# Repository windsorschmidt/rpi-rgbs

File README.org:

#+OPTIONS: toc:nil

* About

TV-compatible RGBS video output board for Raspberry Pi.

[[rpi-rgbs.png?raw=true]]

* Features

- 6-bit R-2R video DAC with buffered 75Ω output on VGA (DE-15) connector
- Composite video sync generator using XNOR logic gates
- Low-pass reconstruction filter audio DAC output on 3.5" phono jack

* Status

Revision 3 tested working with a Raspberry Pi 4.

* License

Circuit schematic and PCB layout are licensed under CERN-OHL-S v2.

See [[LICENSE.txt]].

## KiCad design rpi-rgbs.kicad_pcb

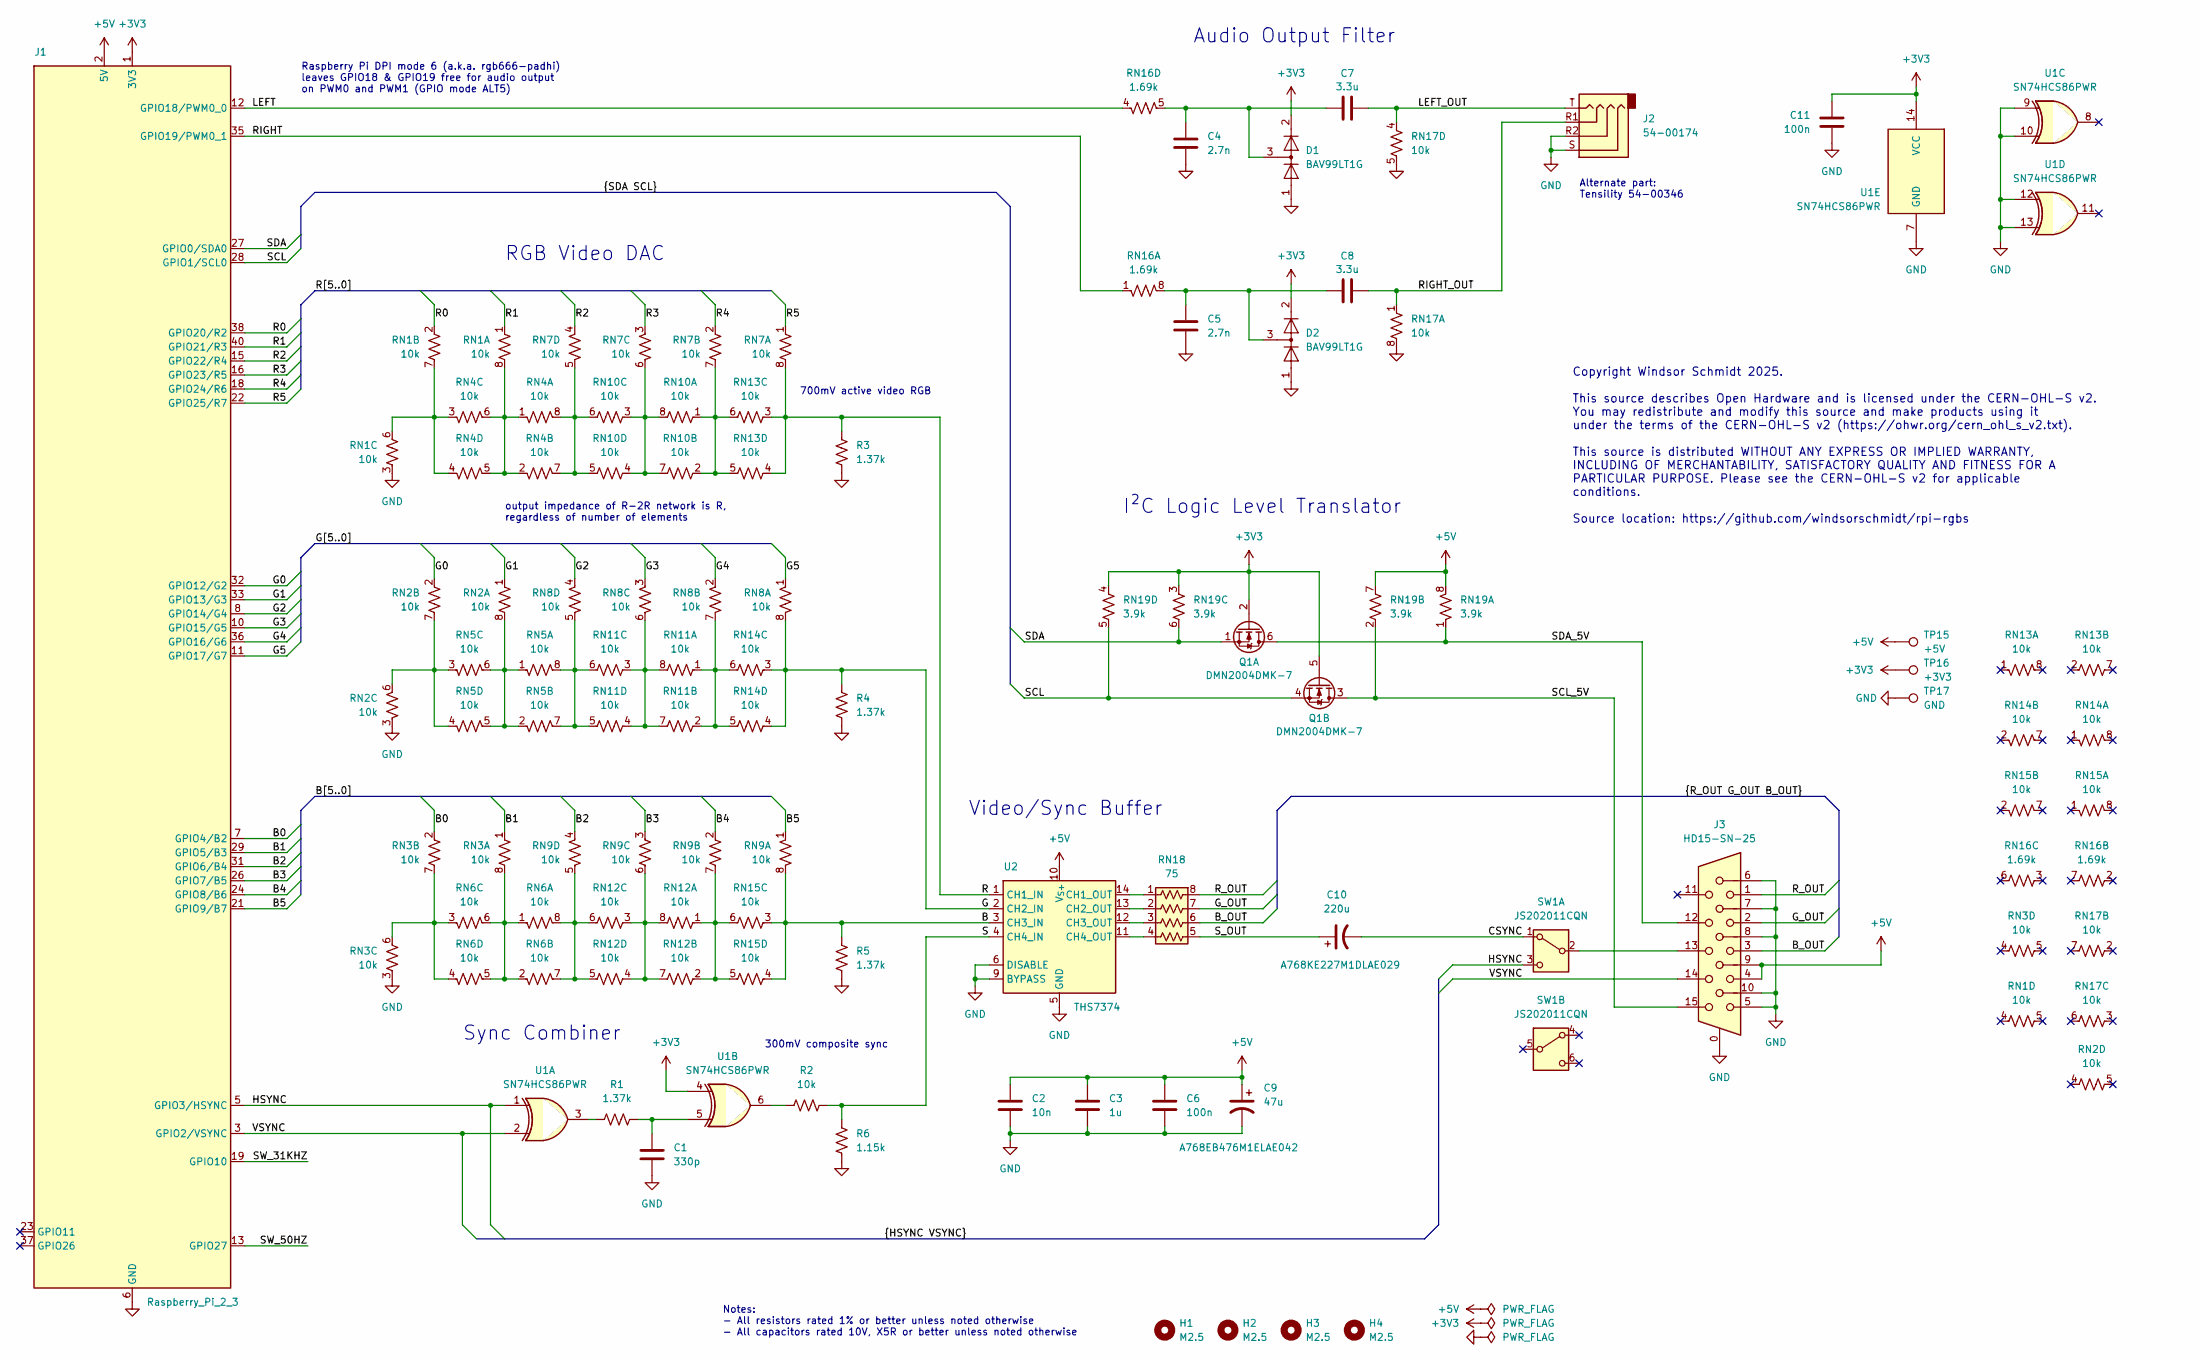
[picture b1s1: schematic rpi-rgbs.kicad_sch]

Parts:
C1: 330p; C_0603_1608Metric
C2: 10n; C_0603_1608Metric
C3: 1u; C_0603_1608Metric
C4, C5: 2.7n; C_0603_1608Metric
C6, C11: 100n; C_0603_1608Metric
C7, C8: 3.3u; C_0805_2012Metric
C9: 47u; CP_Elec_6.3x5.9
C10: 220u; CP_Elec_8x6.2
D1, D2: BAV99LT1G; SOT-23
H1, H2, H3, H4: M2.5; MountingHole_2.7mm_M2.5
J1: Raspberry_Pi_2_3; PinSocket_2x20_P2.54mm_Vertical
J2: 54-00174; Jack_3.5mm_Tensility_54-00174
J3: HD15-SN-25; Connector_Amphenol_L77HDE15SD1CH4FVGA
Q1: DMN2004DMK-7; SOT-23-6
R1, R3, R4, R5: 1.37k; R_0603_1608Metric
R2: 10k; R_0603_1608Metric
R6: 1.15k; R_0603_1608Metric
RN1, RN2, RN3, RN4, RN5, RN6, RN7, RN8, RN9, RN10, RN11, RN12, RN13, RN14, RN15, RN17: 10k; R_Array_Convex_4x0603
RN16: 1.69k; R_Array_Convex_4x0603
RN18: 75; R_Array_Convex_4x0603
RN19: 3.9k; R_Array_Convex_4x0603
SW1: JS202011CQN; SW_CK_JS202011CQN_DPDT_Straight
TP15: +5V; TestPoint_Loop_D1.80mm_Drill1.0mm_Beaded
TP16: +3V3; TestPoint_Loop_D1.80mm_Drill1.0mm_Beaded
TP17: GND; TestPoint_Loop_D1.80mm_Drill1.0mm_Beaded
U1: SN74HCS86PWR; TSSOP-14_4.4x5mm_P0.65mm
U2: THS7374; TSSOP-14_4.4x5mm_P0.65mm

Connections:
+3V3: C11.1, D1.2 (A), D2.2 (A), J1.1 (3V3), Q1.2 (G), Q1.5 (G), RN19.3 (R3.1), RN19.4 (R4.1), TP16.1, U1.4, U1.14 (VCC)
+5V: C2.1, C3.2, C6.1, C9.1, J1.2 (5V), J1.4 (5V), J3.4, J3.9, RN19.7 (R2.2), RN19.8 (R1.2), TP15.1, U2.10 (V_{S+})
/B: R5.1, RN9.8 (R1.2), RN15.3 (R3.1), RN15.4 (R4.1), U2.3 (CH3_IN)
/B0: J1.7 (GPIO4/B2), RN3.2 (R2.1)
/B1: J1.29 (GPIO5/B3), RN3.1 (R1.1)
/B2: J1.31 (GPIO6/B4), RN9.4 (R4.1)
/B3: J1.26 (GPIO7/B5), RN9.3 (R3.1)
/B4: J1.24 (GPIO8/B6), RN9.2 (R2.1)
/B5: J1.21 (GPIO9/B7), RN9.1 (R1.1)
/B_OUT: J3.3, RN18.6
/CSYNC: C10.2, SW1.1 (A)
/G: R4.1, RN8.8 (R1.2), RN14.3 (R3.1), RN14.4 (R4.1), U2.2 (CH2_IN)
/G0: J1.32 (GPIO12/G2), RN2.2 (R2.1)
/G1: J1.33 (GPIO13/G3), RN2.1 (R1.1)
/G2: J1.8 (GPIO14/G4), RN8.4 (R4.1)
/G3: J1.10 (GPIO15/G5), RN8.3 (R3.1)
/G4: J1.36 (GPIO16/G6), RN8.2 (R2.1)
/G5: J1.11 (GPIO17/G7), RN8.1 (R1.1)
/G_OUT: J3.2, RN18.7
/HSYNC: J1.5 (GPIO3/HSYNC), SW1.3 (C), U1.1
/LEFT: J1.12 (GPIO18/PWM0_0), RN16.4 (R4.1)
/LEFT_OUT: C7.2, J2.T, RN17.4 (R4.1)
/R: R3.1, RN7.8 (R1.2), RN13.3 (R3.1), RN13.4 (R4.1), U2.1 (CH1_IN)
/R0: J1.38 (GPIO20/R2), RN1.2 (R2.1)
/R1: J1.40 (GPIO21/R3), RN1.1 (R1.1)
/R2: J1.15 (GPIO22/R4), RN7.4 (R4.1)
/R3: J1.16 (GPIO23/R5), RN7.3 (R3.1)
/R4: J1.18 (GPIO24/R6), RN7.2 (R2.1)
/R5: J1.22 (GPIO25/R7), RN7.1 (R1.1)
/RIGHT: J1.35 (GPIO19/PWM0_1), RN16.1 (R1.1)
/RIGHT_OUT: C8.2, J2.R1, RN17.1 (R1.1)
/R_OUT: J3.1, RN18.8
/S: R2.2, R6.1, U2.4 (CH4_IN)
/SCL: J1.28 (GPIO1/SCL0), Q1.4 (S), RN19.5 (R4.2)
/SCL_5V: J3.15, Q1.3 (D), RN19.2 (R2.1)
/SDA: J1.27 (GPIO0/SDA0), Q1.1 (S), RN19.6 (R3.2)
/SDA_5V: J3.12, Q1.6 (D), RN19.1 (R1.1)
/SW_31KHZ: J1.19 (GPIO10)
/SW_50HZ: J1.13 (GPIO27)
/S_OUT: C10.1, RN18.5
/VSYNC: J1.3 (GPIO2/VSYNC), J3.14, U1.2
GND: C1.2, C2.2, C3.1, C4.2, C5.2, C6.2, C9.2, C11.2, D1.1 (K), D2.1 (K), J1.6 (GND), J1.9 (GND), J1.14 (GND), J1.20 (GND), J1.25 (GND), J1.30 (GND), J1.34 (GND), J1.39 (GND), J2.R2, J2.S, J3.0, J3.5, J3.6, J3.7, J3.8, J3.10, R3.2, R4.2, R5.2, R6.2, RN1.3 (R3.1), RN2.3 (R3.1), RN3.3 (R3.1), RN17.5 (R4.2), RN17.8 (R1.2), TP17.1, U1.7 (GND), U1.9, U1.10, U1.12, U1.13, U2.5 (GND), U2.6 (DISABLE), U2.9 (BYPASS)
unnamed: C1.1, R1.2, U1.5
unnamed: R1.1, U1.3
unnamed: R2.1, U1.6
unnamed: RN1.8 (R1.2), RN4.1 (R1.1), RN4.2 (R2.1), RN4.5 (R4.2), RN4.6 (R3.2)
unnamed: RN1.6 (R3.2), RN1.7 (R2.2), RN4.3 (R3.1), RN4.4 (R4.1)
unnamed: RN2.8 (R1.2), RN5.1 (R1.1), RN5.2 (R2.1), RN5.5 (R4.2), RN5.6 (R3.2)
unnamed: RN2.6 (R3.2), RN2.7 (R2.2), RN5.3 (R3.1), RN5.4 (R4.1)
unnamed: RN3.8 (R1.2), RN6.1 (R1.1), RN6.2 (R2.1), RN6.5 (R4.2), RN6.6 (R3.2)
unnamed: RN3.6 (R3.2), RN3.7 (R2.2), RN6.3 (R3.1), RN6.4 (R4.1)
unnamed: RN7.7 (R2.2), RN10.1 (R1.1), RN10.2 (R2.1), RN13.5 (R4.2), RN13.6 (R3.2)
unnamed: RN7.6 (R3.2), RN10.3 (R3.1), RN10.4 (R4.1), RN10.7 (R2.2), RN10.8 (R1.2)
unnamed: RN4.7 (R2.2), RN4.8 (R1.2), RN7.5 (R4.2), RN10.5 (R4.2), RN10.6 (R3.2)
unnamed: RN8.7 (R2.2), RN11.1 (R1.1), RN11.2 (R2.1), RN14.5 (R4.2), RN14.6 (R3.2)
unnamed: RN8.6 (R3.2), RN11.3 (R3.1), RN11.4 (R4.1), RN11.7 (R2.2), RN11.8 (R1.2)
unnamed: RN5.7 (R2.2), RN5.8 (R1.2), RN8.5 (R4.2), RN11.5 (R4.2), RN11.6 (R3.2)
unnamed: RN9.7 (R2.2), RN12.1 (R1.1), RN12.2 (R2.1), RN15.5 (R4.2), RN15.6 (R3.2)
unnamed: RN9.6 (R3.2), RN12.3 (R3.1), RN12.4 (R4.1), RN12.7 (R2.2), RN12.8 (R1.2)
unnamed: RN6.7 (R2.2), RN6.8 (R1.2), RN9.5 (R4.2), RN12.5 (R4.2), RN12.6 (R3.2)
unnamed: C5.1, C8.1, D2.3 (K), RN16.8 (R1.2)
unnamed: C4.1, C7.1, D1.3 (K), RN16.5 (R4.2)
unnamed: J3.13, SW1.2 (B)
unnamed: RN18.1, U2.14 (CH1_OUT)
unnamed: RN18.2, U2.13 (CH2_OUT)
unnamed: RN18.3, U2.12 (CH3_OUT)
unnamed: RN18.4, U2.11 (CH4_OUT)

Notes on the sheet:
Notes: - All resistors rated 1% or better unless noted otherwise - All capacitors rated 10V, X5R or better unless noted otherwise
Alternate part: Tensility 54-00346
Raspberry Pi DPI mode 6 (a.k.a. rgb666-padhi) leaves GPIO18 & GPIO19 free for audio output on PWM0 and PWM1 (GPIO mode ALT5)
700mV active video RGB
Audio Output Filter
Sync Combiner
300mV composite sync
I²C Logic Level Translator
RGB Video DAC
Copyright Windsor Schmidt 2025. This source describes Open Hardware and is licensed under the CERN-OHL-S v2. You may redistribute and modify this source and make products using it under the terms of the CERN-OHL-S v2 (https://ohwr.org/cern_ohl_s_v2.txt). This source is distributed WITHOUT ANY EXPRE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
output impedance of R-2R network is R, regardless of number of elements
Video/Sync Buffer

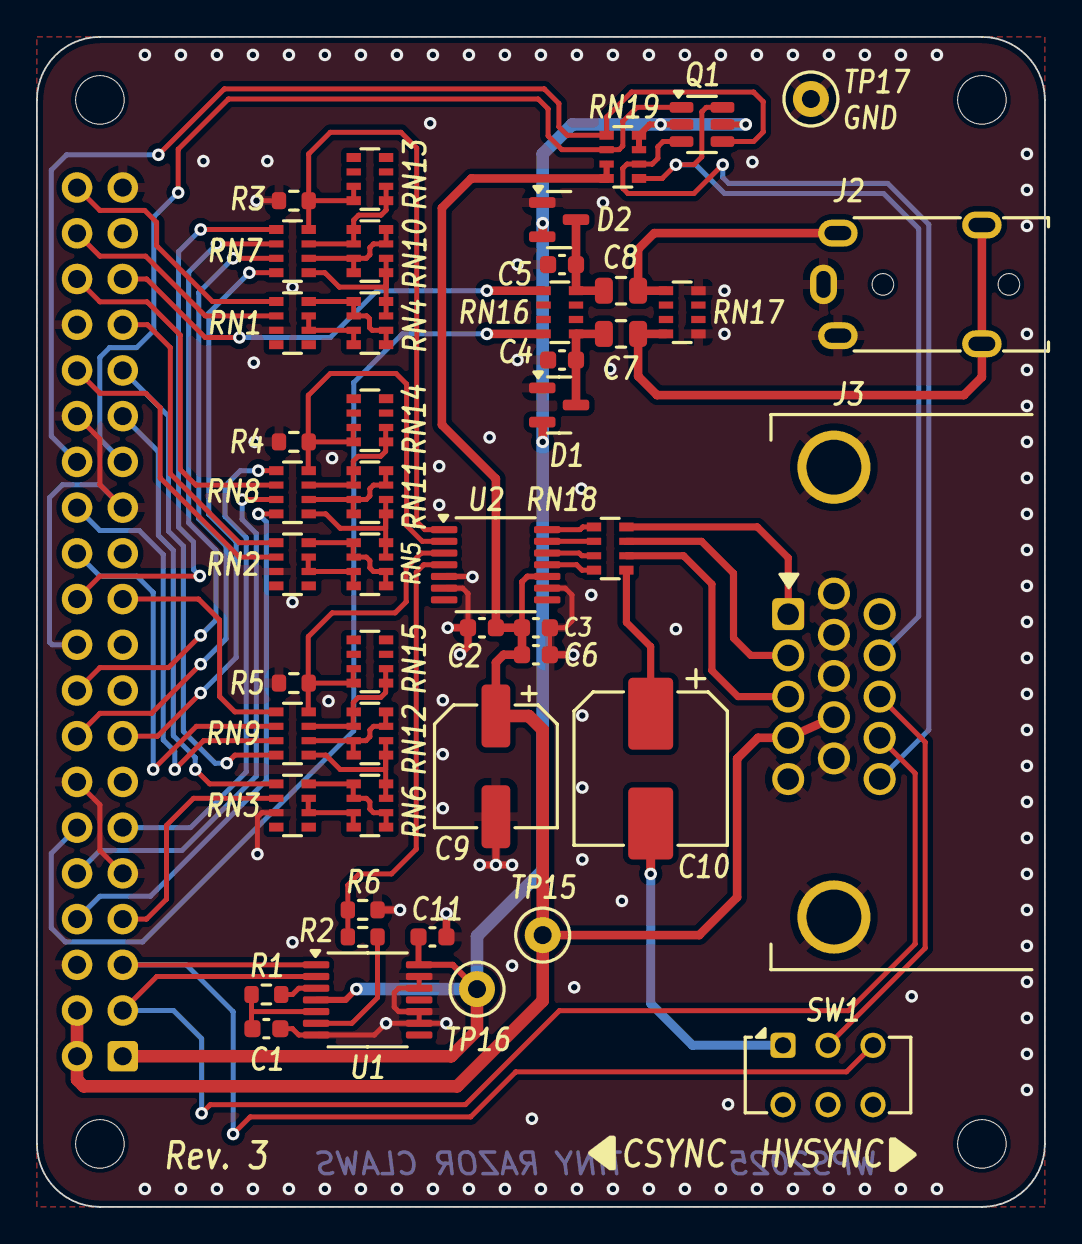
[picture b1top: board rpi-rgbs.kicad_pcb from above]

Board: 2 copper layers, 56.0 x 65.0 mm, 52 parts (1 on the bottom side), 65 nets.

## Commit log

2025-08-19 tweak silkscreen
2025-08-20 update pcb image
